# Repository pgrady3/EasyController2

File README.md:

### The EasyController3 has been released. It is cheaper, more efficient, and uses parts that are in-stock. [Check it out here!](https://github.com/pgrady3/EasyController3)

# EasyController2

*NOTE: Check out the [EasyTelemetry](https://github.com/pgrady3/EasyTelemetry) project for a similarly simple board for logging vehicle voltage/current/speed/position.*

A simple brushless (BLDC) sensored motor controller. Intended to drive electric vehicles such as electric bikes, skateboards, or Eco-Marathon vehicles. The controller can handle nominal power of about 1kW.

This controller was designed to fill a gap in publicly released motor controller designs. It is simple enough to serve as an introduction to power electronics, and to hopefully allow those unfamiliar with motors to get their feet wet. To this end, the controller is designed to be as simple and easy-to-understand as possible. Thus it lacks more complex features such as sensorless control or current-feedback control, however these features can be easily added with some modifications. This project is meant as a learning tool and a foundation to potentially build more complex designs from.

This project is a successor to the [2016 controller](http://www.duke-ev.org/blog/2016/11/27/the-2016-motor-controller) released on the DEV website. This design is dramatically easier to solder, more robust, and simpler, while still achieving the same functionality. We strongly encourage use of this new design.

## Specifications
* 15v-60v operation
* 20A continuous current, 40A burst (more with heatsinking)
* All through-hole design. Easy to solder!
* Socket for automotive fuse
* Automatic hall sensor identification
* Extremely simple code. <200 lines with comments
* Duty-cycle control
* Teensy 3.2 microcontroller
* L6387E gate drivers
* IRFB7730 MOSFETS
* BOM cost of 70 USD
* Totally open source

## Schematic

## Board

## Software Used

* PCB layout: [Eagle](https://www.autodesk.com/products/eagle/free-download)
* Compiler: [Arduino](https://www.arduino.cc/) with [PJRC Teensyduino add-on](https://www.pjrc.com/teensy/td_download.html)

## Assembly

This respository includes Gerber files which can be directly submitted to PCB manufacturers. We recommend Chinese manufacturers such as [AllPCB](https://www.allpcb.com/) or [JLCPCB](https://jlcpcb.com/). The repository also includes a Bill of Materials (BOM) with Digikey part numbers to order from.

Assembly is straightforward. However, it is recommended to cut the VIN-VUSB trace on the [underside of the Teensy](https://www.pjrc.com/teensy/card7b_rev1.pdf). Cutting the trace means that the Teensy can no longer be powered over USB. This is a safety procaution to prevent the controller feeding power backwards into your computer's USB port. 

## Design Improvements

The EasyController2 was designed with absolute simplicity in mind. It is meant to be as easy to understand as possible at the expense of additional features.

However, this design is very similar to the [world record motor controller](https://github.com/DukeElectricVehicles/dev-eagle/tree/master/Controller2019_Guinness) that powered DEV's vehicle [Eta to a Guinness World Record](https://pratt.duke.edu/about/news/duke-student-team-wins-second-guinness-world-record-vehicle-efficiency). Improvements to the world record design include:

* Lower quiescent power. The EasyController2 draws about 1 watt of quiescent power. As Eta's nomial power consumption was only 19 watts, this is too high. This can be improved with slower clocking of the microcontroller and more intelligent power supply design.
* Hybrid sensor/sensorless control. All electric vehicles need sensors for initial motor startup. However at high speed, hall sensors become noisy and do not provide as clean of trasitions as BEMF sensorless monitoring.
* Current feedback control. It is critical that the motor be run in the correct operating range to minimize resistance versus magnetic losses in the motor. This requires a current control loop, keeping the motor operating at the optimal power level.
* Synchronous switching. The EasyController2 only PWMs the high-side MOSFET, and in off times, the current flows through the low-side body diode. This is known as non-synchronous switching, and results in a roughly 0.7v loss during switch off-times. This loss becomes more significant at low duty cycles. Performing [synchronous switching](https://www.digikey.com/en/articles/techzone/2015/sep/what-you-need-to-know-about-synchronous-voltage-regulation) is only possible with current feedback control, and was thus omitted from the EasyController for simplicity. With synchronous switching and a current feedback loop, regen can be accomplished.

These improvements are only critical for those seeking to squeeze the last few percent of efficiency out of their powertrain. However, for most applications, the EasyController2 is more than sufficient. These improvements are left as an excercise to future electrical engineers to keep with the spirit of the Shell Eco-Marathon.

## Contact Us

This controller was designed by Patrick Grady from Duke Electric Vehicles. If you need help or clarification, please [send us a message on our website.](http://www.duke-ev.org/dev-contact-us)

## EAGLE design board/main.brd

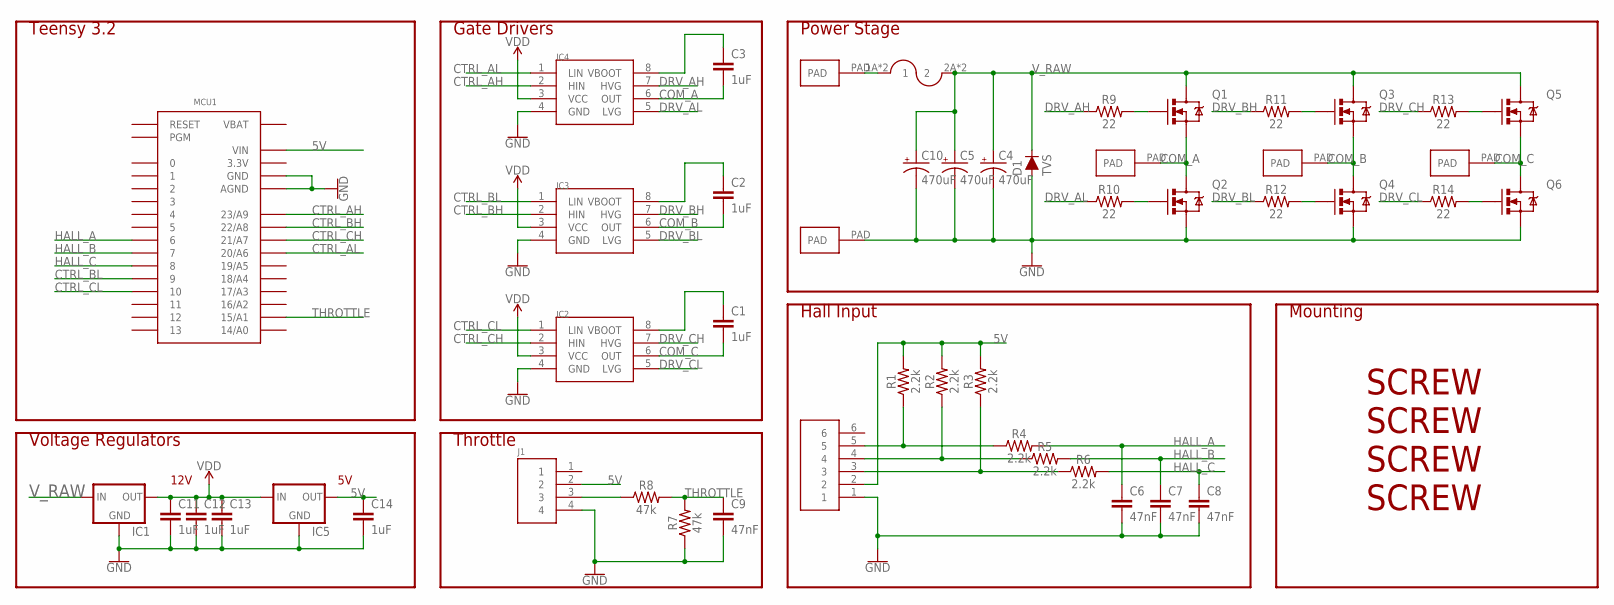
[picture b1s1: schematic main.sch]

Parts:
C1, C2, C3, C11, C12, C13, C14: 1uF; CAP-PTH-SMALL-KIT
C4, C5, C10: 470uF; CPOL-RADIAL-5MM-10MM
C6, C7, C8, C9: 47nF; CAP-PTH-SMALL-KIT
D1: TVS; DIODE-1N4001
IC1: V_REG_78XX; V78W_BACKWARDS
IC2, IC3, IC4: L6387EDIP8; DIP762W53P254L1092H508Q8B
IC5: V_REG_78XXTO-92_UNTESTED; TO-92
J1: HEADER4VALULOK; 4PINVALULOK
J2: HEADER6; 6PINVALULOK
J3: FUSE; AUTO_FUSE
MCU1: TEENSY_3.0_BASIC
Q1, Q2, Q3, Q4, Q5, Q6: MOSFET-NCHANNELTO-220-FLAT; TO-220-FLAT
R1, R2, R3, R4, R5, R6: 2.2k; AXIAL-0.3
R7, R8: 47k; AXIAL-0.3
R9, R10, R11, R12, R13, R14: 22; AXIAL-0.3
U$4, U$5, U$6, U$7, U$8: PAD
U$10, U$11, U$12, U$13: SCREW; M3HOLE

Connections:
3.3V: MCU1.3.3V, MCU1.3.3V1 (3.3V)
5V: C14.1, IC5.1 (OUT), J1.2, J2.2, MCU1.VIN, R1.P$2 (2), R2.P$2 (2), R3.P$2 (2)
COM_A: C3.2, IC4.6 (OUT), Q1.3 (S), Q2.2 (D), Q2.PAD (D), U$6.PAD
COM_B: C2.2, IC3.6 (OUT), Q3.3 (S), Q4.2 (D), Q4.PAD (D), U$7.PAD
COM_C: C1.2, IC2.6 (OUT), Q5.3 (S), Q6.2 (D), Q6.PAD (D), U$8.PAD
CTRL_AH: IC4.2 (HIN), MCU1.23/A9
CTRL_AL: IC4.1 (LIN), MCU1.20/A6
CTRL_BH: IC3.2 (HIN), MCU1.22/A8
CTRL_BL: IC3.1 (LIN), MCU1.9
CTRL_CH: IC2.2 (HIN), MCU1.21/A7
CTRL_CL: IC2.1 (LIN), MCU1.10
DRV_AH: IC4.7 (HVG), R9.P$1 (1)
DRV_AL: IC4.5 (LVG), R10.P$1 (1)
DRV_BH: IC3.7 (HVG), R11.P$1 (1)
DRV_BL: IC3.5 (LVG), R12.P$1 (1)
DRV_CH: IC2.7 (HVG), R13.P$1 (1)
DRV_CL: IC2.5 (LVG), R14.P$1 (1)
GND: C4.-, C5.-, C6.2, C7.2, C8.2, C9.2, C10.-, C11.2, C12.2, C13.2, C14.2, D1.A, IC1.GND, IC2.4 (GND), IC3.4 (GND), IC4.4 (GND), IC5.2 (GND), J1.4, J2.1, MCU1.AGND, MCU1.GND, MCU1.GND1 (GND), Q2.3 (S), Q4.3 (S), Q6.3 (S), R7.P$1 (1), U$5.PAD
HALL_A: C6.1, MCU1.6, R4.P$2 (2)
HALL_B: C7.1, MCU1.7, R5.P$2 (2)
HALL_C: C8.1, MCU1.8, R6.P$2 (2)
unnamed: C1.1, IC2.8 (VBOOT)
unnamed: J2.3, R3.P$1 (1), R6.P$1 (1)
unnamed: C2.1, IC3.8 (VBOOT)
unnamed: J2.4, R2.P$1 (1), R5.P$1 (1)
unnamed: C3.1, IC4.8 (VBOOT)
unnamed: J2.5, R1.P$1 (1), R4.P$1 (1)
unnamed: J1.3, R8.P$1 (1)
unnamed: Q1.1 (G), R9.P$2 (2)
unnamed: Q2.1 (G), R10.P$2 (2)
unnamed: Q3.1 (G), R11.P$2 (2)
unnamed: Q4.1 (G), R12.P$2 (2)
unnamed: Q5.1 (G), R13.P$2 (2)
unnamed: Q6.1 (G), R14.P$2 (2)
THROTTLE: C9.1, MCU1.15/A1, R7.P$2 (2), R8.P$2 (2)
VBAT: MCU1.VBAT
VDD: C11.1, C12.1, C13.1, IC1.OUT, IC2.3 (VCC), IC3.3 (VCC), IC4.3 (VCC), IC5.3 (IN)
V_PREFUSE: J3.1A (1), J3.1B (1), U$4.PAD
V_RAW: C4.+, C5.+, C10.+, D1.C, IC1.IN, J3.2A (2), J3.2B (2), Q1.2 (D), Q1.PAD (D), Q3.2 (D), Q3.PAD (D), Q5.2 (D), Q5.PAD (D)

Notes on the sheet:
Power Stage
Hall Input
Gate Drivers
Throttle
Teensy 3.2
Voltage Regulators
12V
Mounting

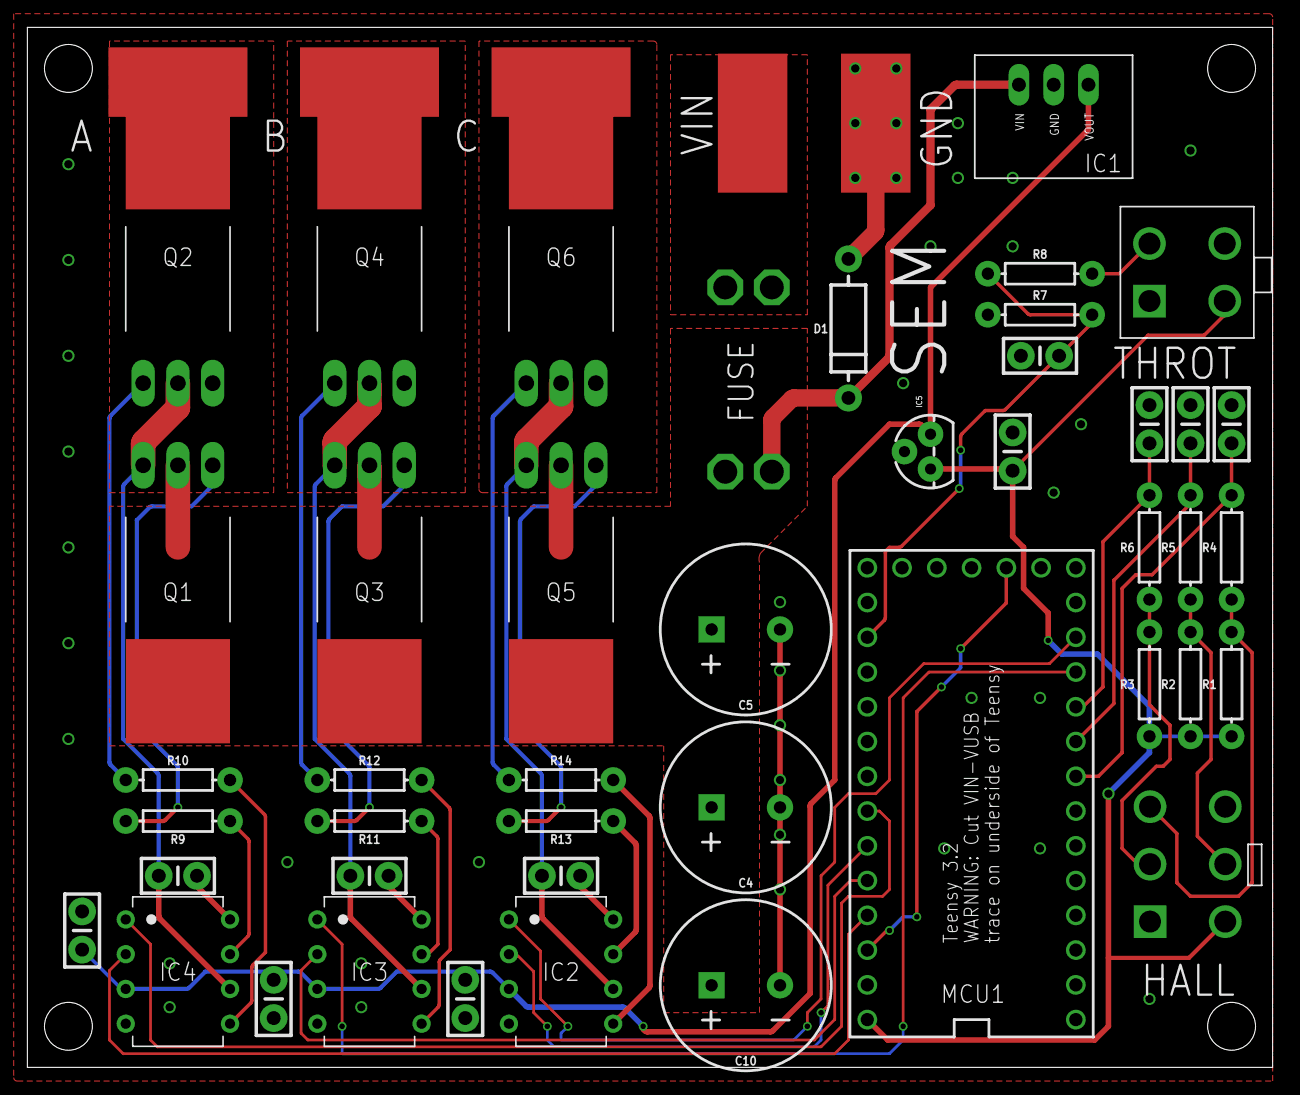
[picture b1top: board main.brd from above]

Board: 2 copper layers, 91.0 x 76.0 mm, 53 parts (0 on the bottom side), 38 nets.

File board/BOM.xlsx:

Digikey part # | Designator | Qty | Price | Description
497-6217-5-ND | IC2,IC3,IC4 | 3 | 1.66 | Gate driver |  |  |  | 4.9799999999999995 |  | 70.749999999999986
445-173257-1-ND | C1,C2,C3,C11,C12,C13,C14 | 7 | 0.33 | 1uF cap |  |  |  | 2.31
IRFB7730PBF-ND | Q1,Q2,Q3,Q4,Q5,Q6 | 6 | 3.51 | NFET |  |  |  | 21.06
P6KE68CALFCT-ND | D1 | 1 | 0.47 | TVS Diode |  |  |  | 0.47
565-3994-ND | C4,C5,C10 | 3 | 1.1499999999999999 | 470uF cap |  |  |  | 3.4499999999999997
CF14JT2K20CT-ND | R1,R2,R3,R4,R5,R6 | 6 | 0.1 | 2.2k resistor |  |  |  | 0.60000000000000009
BC1082CT-ND | C6,C7,C8,C9 | 3 | 0.16 | 47nF cap |  |  |  | 0.48
36-3557-2-ND | J3 | 1 | 1.03 | Fuse holder |  |  |  | 1.03
1470-4533-ND | IC1 | 1 | 8 | Voltage Regulator |  |  |  | 8
CF14JT47K0CT-ND | R7,R8 | 2 | 0.1 | 47k resistor |  |  |  | 0.2
1568-1231-ND | MCU1 | 1 | 22.5 | Teensy 3.2 |  |  |  | 22.5
CF14JT22R0CT-ND | R9,R10,R11,R12,R13,R14 | 6 | 0.1 | 22 ohm |  |  |  | 0.60000000000000009
497-1184-1-ND | IC5 | 1 | 0.35 | 5V Linear reg |  |  |  | 0.35
S1012EC-14-ND |  | 2 | 0.31 | 14 pin male header |  |  |  | 0.62
S7012-ND |  | 2 | 0.91 | 14 pin female header |  |  |  | 1.82
A30603-ND | J1 | 1 | 0.68 | 4 pin female connector VAL-U-LOK |  |  |  | 0.68
A30604-ND | J2 | 1 | 0.65 | 6 pin female connector VAL-U-LOK |  |  |  | 0.65
A30591-ND |  | 1 | 0.21 | 4 pin male connector VAL-U-LOK |  |  |  | 0.21
A30592-ND |  | 1 | 0.24 | 6 pin male connector VAL-U-LOK |  |  |  | 0.24
A99267CT-ND |  | 10 | 0.05 | VAL-U-LOK crimp pin |  |  |  | 0.5
345-1092-ND‎ |  | 1 | 1.46 | Heatsink, optional
345-1006-ND |  | 1 | 3.82 | Thermal paste, for heatsink

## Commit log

2019-03-13 Initial commit. Copied from controller 1_1
2019-03-13 Flipped connectors, changed silkscreen
2019-03-13 Initial readme
2019-03-13 Changed names and silkscreen
2019-03-13 AllPCB submit for CNS
2019-03-14 Added connectors to BOM
2019-03-14 Added schematic PDF
2019-11-24 Better readme
2019-11-24 Readme tweak
2019-11-24 More readme tweaks
2019-11-24 Readme updates
2019-11-24 Readme further work
2019-11-25 Added synchronous readme
2021-01-05 Added EasyTelemetry reference
2022-12-13 Updated to reflect EasyController3 in progress
2023-03-30 EasyController3 released
2023-03-30 Released of EasyController3

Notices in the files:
parts and their libraries:
SparkFun-Capacitors: Licensing: Creative Commons ShareAlike 4.0 International - https://creativecommons.org/licenses/by-sa/4.0
